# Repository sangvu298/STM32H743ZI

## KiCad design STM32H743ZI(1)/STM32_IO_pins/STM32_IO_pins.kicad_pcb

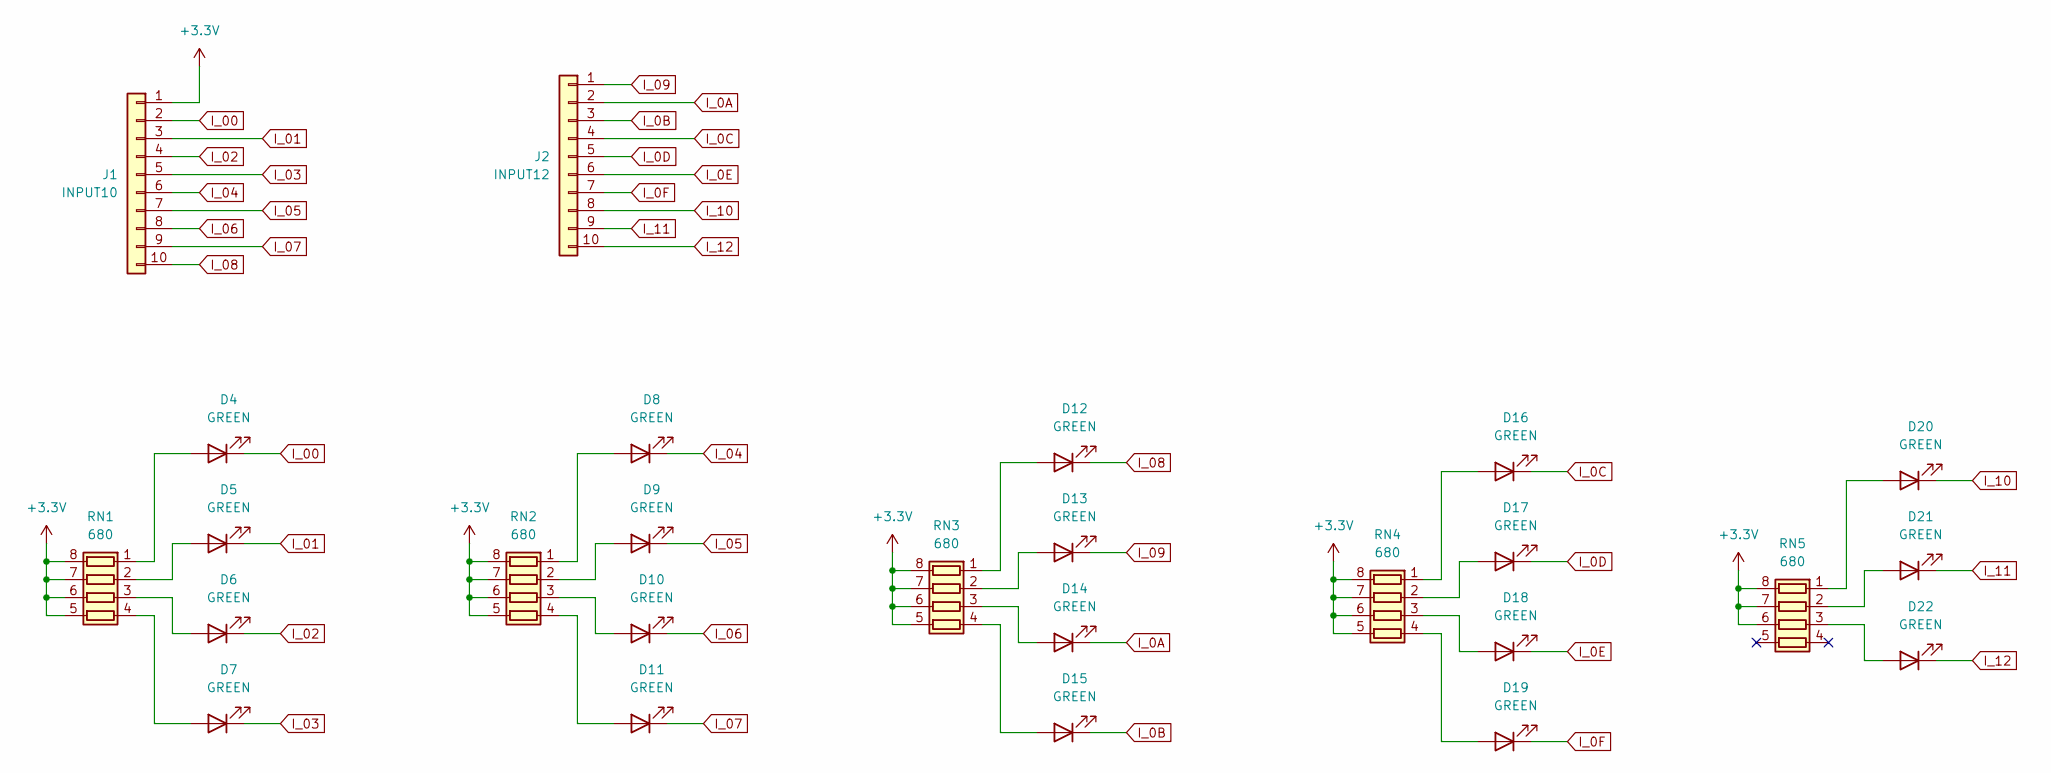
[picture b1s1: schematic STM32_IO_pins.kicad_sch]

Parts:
D4, D5, D6, D7, D8, D9, D10, D11, D12, D13, D14, D15, D16, D17, D18, D19, D20, D21, D22: GREEN; LED_0805_2012Metric
J1: INPUT10; PinHeader_1x10_P2.54mm_Horizontal
J2: INPUT12; PinHeader_1x10_P2.54mm_Horizontal
RN1, RN2, RN3, RN4, RN5: 680; R_Array_Concave_4x0603

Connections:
+3.3V: J1.1, RN1.5 (R4.2), RN1.6 (R3.2), RN1.7 (R2.2), RN1.8 (R1.2), RN2.5 (R4.2), RN2.6 (R3.2), RN2.7 (R2.2), RN2.8 (R1.2), RN3.5 (R4.2), RN3.6 (R3.2), RN3.7 (R2.2), RN3.8 (R1.2), RN4.5 (R4.2), RN4.6 (R3.2), RN4.7 (R2.2), RN4.8 (R1.2), RN5.6 (R3.2), RN5.7 (R2.2), RN5.8 (R1.2)
I_00: D4.1 (K), J1.2
I_0A: D14.1 (K), J2.2
I_0B: D15.1 (K), J2.3
I_0C: D16.1 (K), J2.4
I_0D: D17.1 (K), J2.5
I_0E: D18.1 (K), J2.6
I_0F: D19.1 (K), J2.7
I_01: D5.1 (K), J1.3
I_02: D6.1 (K), J1.4
I_03: D7.1 (K), J1.5
I_04: D8.1 (K), J1.6
I_05: D9.1 (K), J1.7
I_06: D10.1 (K), J1.8
I_07: D11.1 (K), J1.9
I_08: D12.1 (K), J1.10
I_09: D13.1 (K), J2.1
I_10: D20.1 (K), J2.8
I_11: D21.1 (K), J2.9
I_12: D22.1 (K), J2.10
unnamed: D4.2 (A), RN1.1 (R1.1)
unnamed: D5.2 (A), RN1.2 (R2.1)
unnamed: D6.2 (A), RN1.3 (R3.1)
unnamed: D7.2 (A), RN1.4 (R4.1)
unnamed: D8.2 (A), RN2.1 (R1.1)
unnamed: D9.2 (A), RN2.2 (R2.1)
unnamed: D10.2 (A), RN2.3 (R3.1)
unnamed: D11.2 (A), RN2.4 (R4.1)
unnamed: D12.2 (A), RN3.1 (R1.1)
unnamed: D13.2 (A), RN3.2 (R2.1)
unnamed: D14.2 (A), RN3.3 (R3.1)
unnamed: D15.2 (A), RN3.4 (R4.1)
unnamed: D16.2 (A), RN4.1 (R1.1)
unnamed: D17.2 (A), RN4.2 (R2.1)
unnamed: D18.2 (A), RN4.3 (R3.1)
unnamed: D19.2 (A), RN4.4 (R4.1)
unnamed: D20.2 (A), RN5.1 (R1.1)
unnamed: D21.2 (A), RN5.2 (R2.1)
unnamed: D22.2 (A), RN5.3 (R3.1)

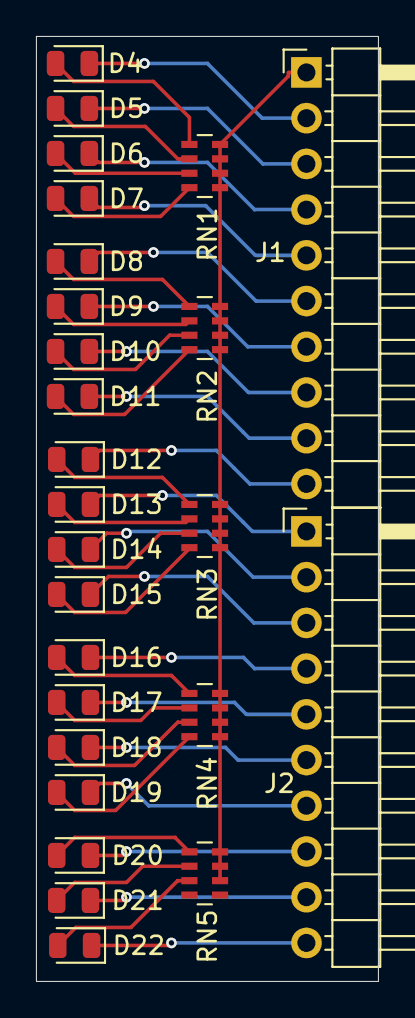
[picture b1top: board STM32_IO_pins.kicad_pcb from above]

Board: 2 copper layers, 19.0 x 52.5 mm, 26 parts (0 on the bottom side), 39 nets.

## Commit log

2024-12-19 Create STM32H743ZI(2)
